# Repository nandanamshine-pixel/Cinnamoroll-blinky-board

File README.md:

# Cinnamoroll-blinky-board
A blinky board in the shape of cinnamoroll!!
A 555 timer LED chaser in a PCB shaped in the shape of cinnamoroll. 
The 10 LEDs glow in a sequence using a potentiometer/variable resistor

# Components
- 555 Timer IC
- 10x LEDs of any color
- CD4017 IC (a decade counter for the LEDs)
- 1 electrolytic capacitor
- 1 normal capacitor
- 2x resistors (1kΩ and 470Ω)
- Power connector
- 1 potentiometer

# Softwares used
KiCAD 9.0 --> PCB and Schematic

# Working
The 555 timer works in astable mode and gets clock signals. The CD4017 IC then 'counts to 10' (as a decade counter) by activating its 10 outputs one at a time, thereby making the LEDs light up one by one in a 'chasing' manner. The potentiometer is used to control the speed of this chase.

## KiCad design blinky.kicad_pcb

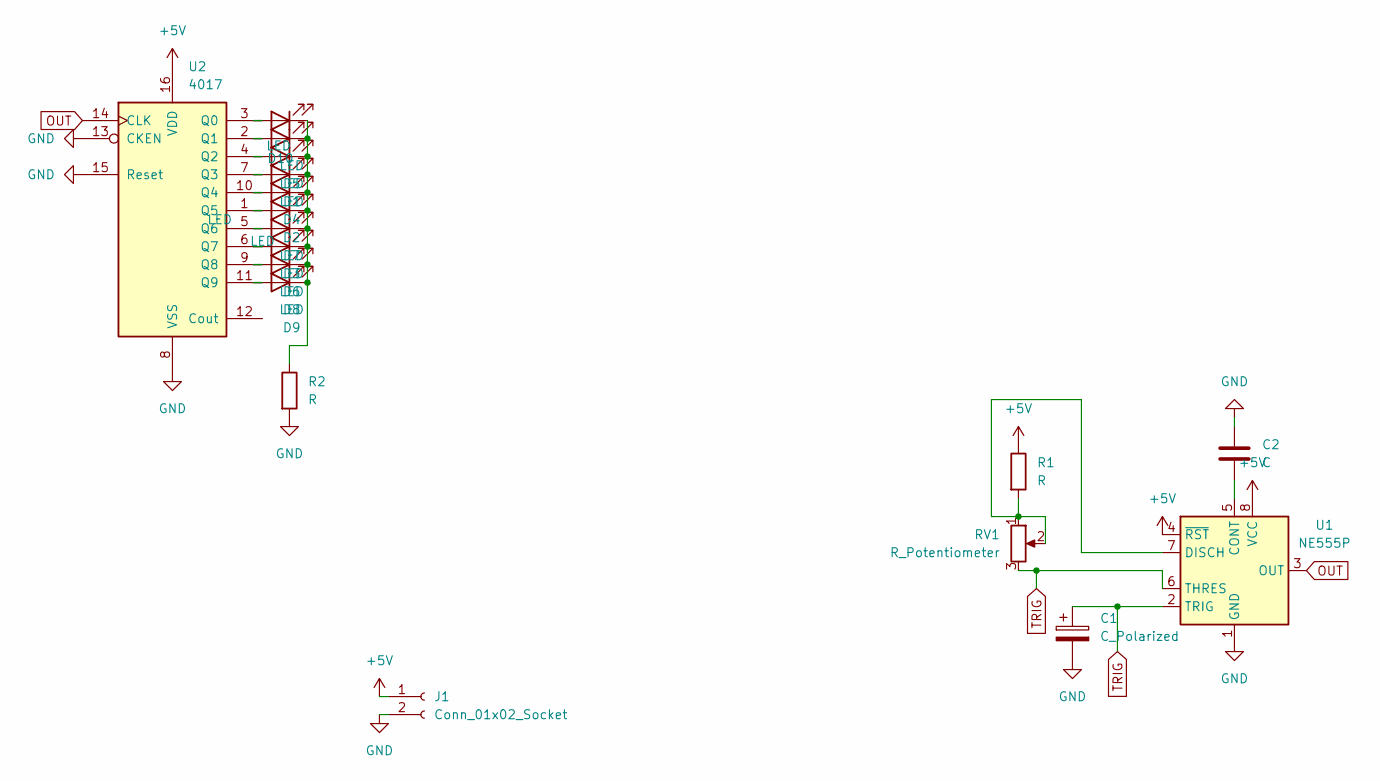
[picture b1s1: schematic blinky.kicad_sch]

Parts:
C1: C_Polarized; C_Radial_D5.0mm_H11.0mm_P2.00mm
C2: C; C_Disc_D5.0mm_W2.5mm_P5.00mm
D1, D2, D3, D4, D5, D6, D7, D8, D9, D10: LED; LED_D5.0mm
J1: Conn_01x02_Socket; PinSocket_1x02_P2.54mm_Vertical
R1, R2: R; R_Axial_DIN0207_L6.3mm_D2.5mm_P7.62mm_Horizontal
RV1: R_Potentiometer; Potentiometer_Piher_PT-6-V_Vertical
U1: NE555P; DIP-8_W7.62mm
U2: 4017; N16

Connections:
+5V: J1.1, R1.1, U1.4 (~RST), U1.8 (VCC), U2.16 (VDD)
GND: C1.2, C2.1, J1.2, R2.2, U1.1 (GND), U2.8 (VSS), U2.13 (CKEN), U2.15 (Reset)
unnamed: D1.2 (A), U2.4 (Q2)
unnamed: D1.1 (K), D2.1 (K), D3.1 (K), D4.1 (K), D5.1 (K), D6.1 (K), D7.1 (K), D8.1 (K), D9.1 (K), D10.1 (K), R2.1
unnamed: D2.2 (A), U2.10 (Q4)
unnamed: D3.2 (A), U2.5 (Q6)
unnamed: D4.2 (A), U2.7 (Q3)
unnamed: D5.2 (A), U2.2 (Q1)
unnamed: D6.2 (A), U2.6 (Q7)
unnamed: D7.2 (A), U2.1 (Q5)
unnamed: D8.2 (A), U2.9 (Q8)
unnamed: D9.2 (A), U2.11 (Q9)
unnamed: D10.2 (A), U2.3 (Q0)
unnamed: C2.2, U1.5 (CONT)
unnamed: R1.2, RV1.1, RV1.2, U1.7 (DISCH)
OUT: U1.3 (OUT), U2.14 (CLK)
TRIG: C1.1, RV1.3, U1.2 (TRIG), U1.6 (THRES)

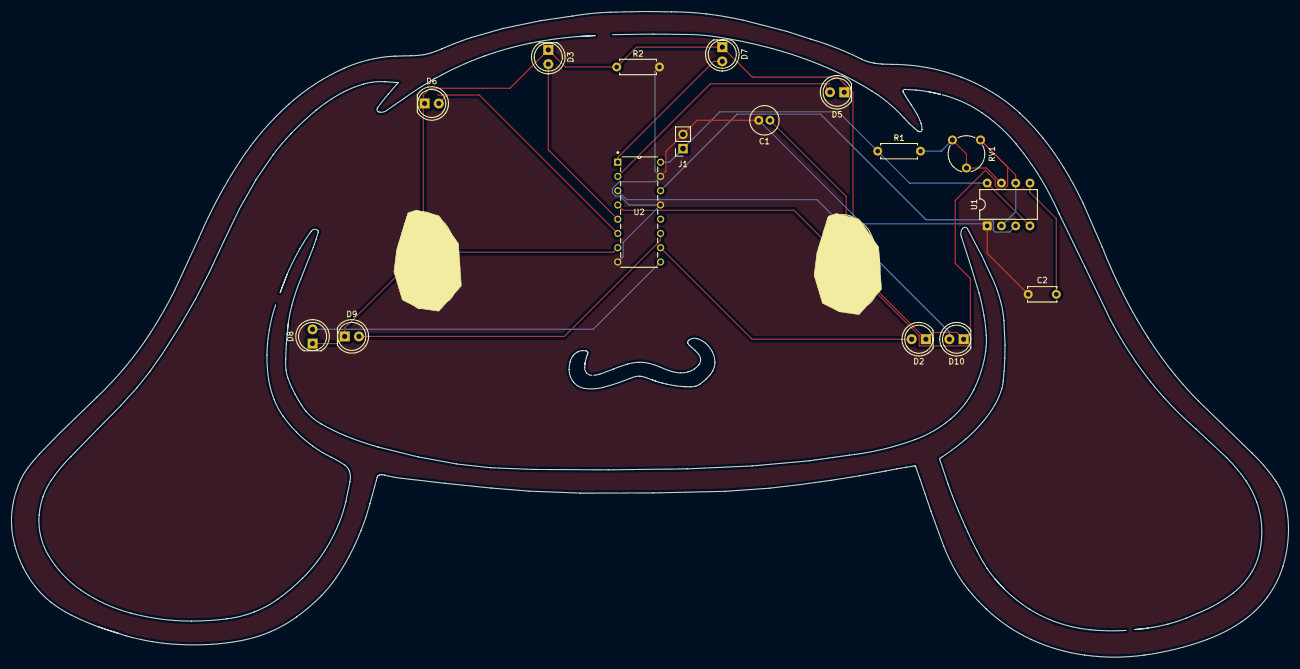
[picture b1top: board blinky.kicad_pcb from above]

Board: 2 copper layers, 227.5 x 115.0 mm, 18 parts (0 on the bottom side), 17 nets.

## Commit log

2026-04-09 3d image
2026-04-09 pcb upload
2026-04-09 Actual pcb file
2026-04-09 Project file
2026-04-09 Schematic upload
2026-04-09 Gerber files upload
2026-04-13 Removed wrong file
2026-04-13 BOM.csv added
